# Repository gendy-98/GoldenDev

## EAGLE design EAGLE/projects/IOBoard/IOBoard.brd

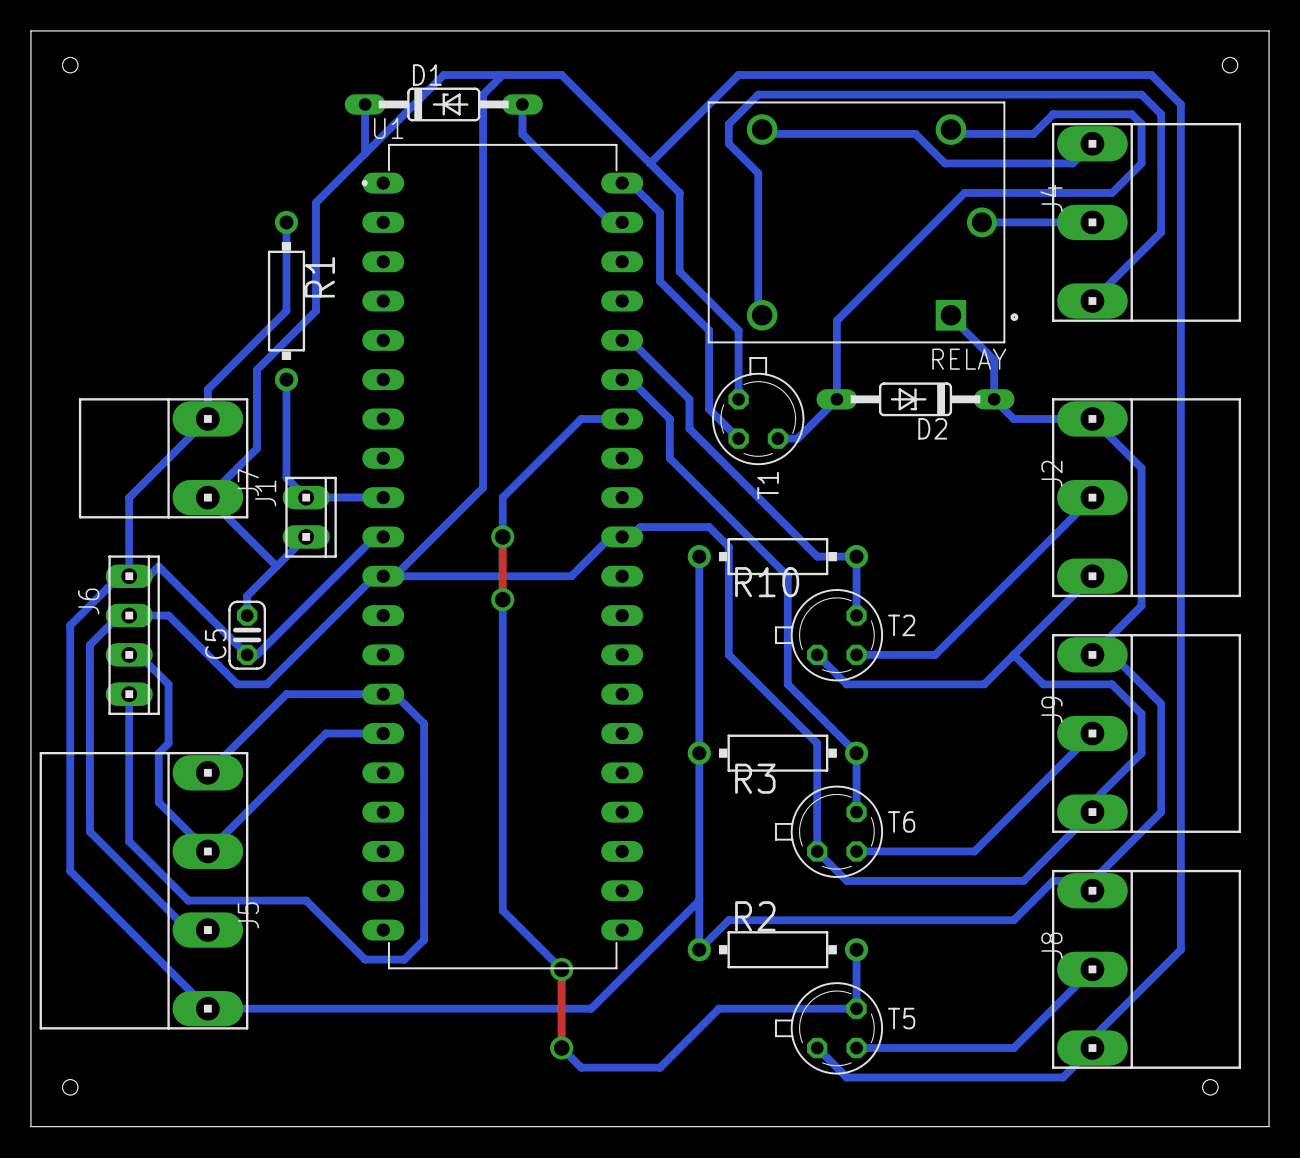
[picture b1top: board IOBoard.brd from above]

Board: 2 copper layers, 80.0 x 70.8 mm, 21 parts (0 on the bottom side), 17 nets.

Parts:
C5: C025-024X044
D1, D2: 1N821; DO35Z10
J1: 10X02MTA
J2, J4, J8, J9: 10X05MTA_MYV
J5: 10X07MTA_MYV
J6: 10X04MTA
J7: 10X03MTA_MYV
R1, R2, R3, R10: HPS58
RELAY: SRD-05VDC-SL-C; RELAY_SRD-05VDC-SL-C
T1, T2, T5, T6: 2N2222; TO18
U1: ATMEGA32A-PU; DIP1540W47P254L5320H635Q40B

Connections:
GND: C5.2, D1.C, J1.1, J2.1, J5.5, J6.3, J7.3, J8.1, J9.1, T1.1, T2.1, T5.1, T6.1, U1.11, U1.31
unnamed: J4.5, RELAY.NO
unnamed: J4.3, RELAY.COM
unnamed: J4.1, RELAY.NC
unnamed: D2.A, RELAY.A2, T1.3
unnamed: J8.3, T5.2
unnamed: J2.3, T2.2
unnamed: J9.3, T6.2
PA0: T1.2, U1.40
PA1: D1.A, U1.39
PA4: R10.2, T2.3, U1.36
PA5: R3.2, T6.3, U1.35
PA6: R2.2, T5.3, U1.34
RST: J1.2, R1.2, U1.9
RX: J5.3, J6.2, U1.15
TX: J5.1, J6.1, U1.14
VCC: C5.1, D2.C, J2.5, J5.7, J6.4, J7.1, J8.5, J9.5, R1.1, R2.1, R3.1, R10.1, RELAY.A1, U1.10

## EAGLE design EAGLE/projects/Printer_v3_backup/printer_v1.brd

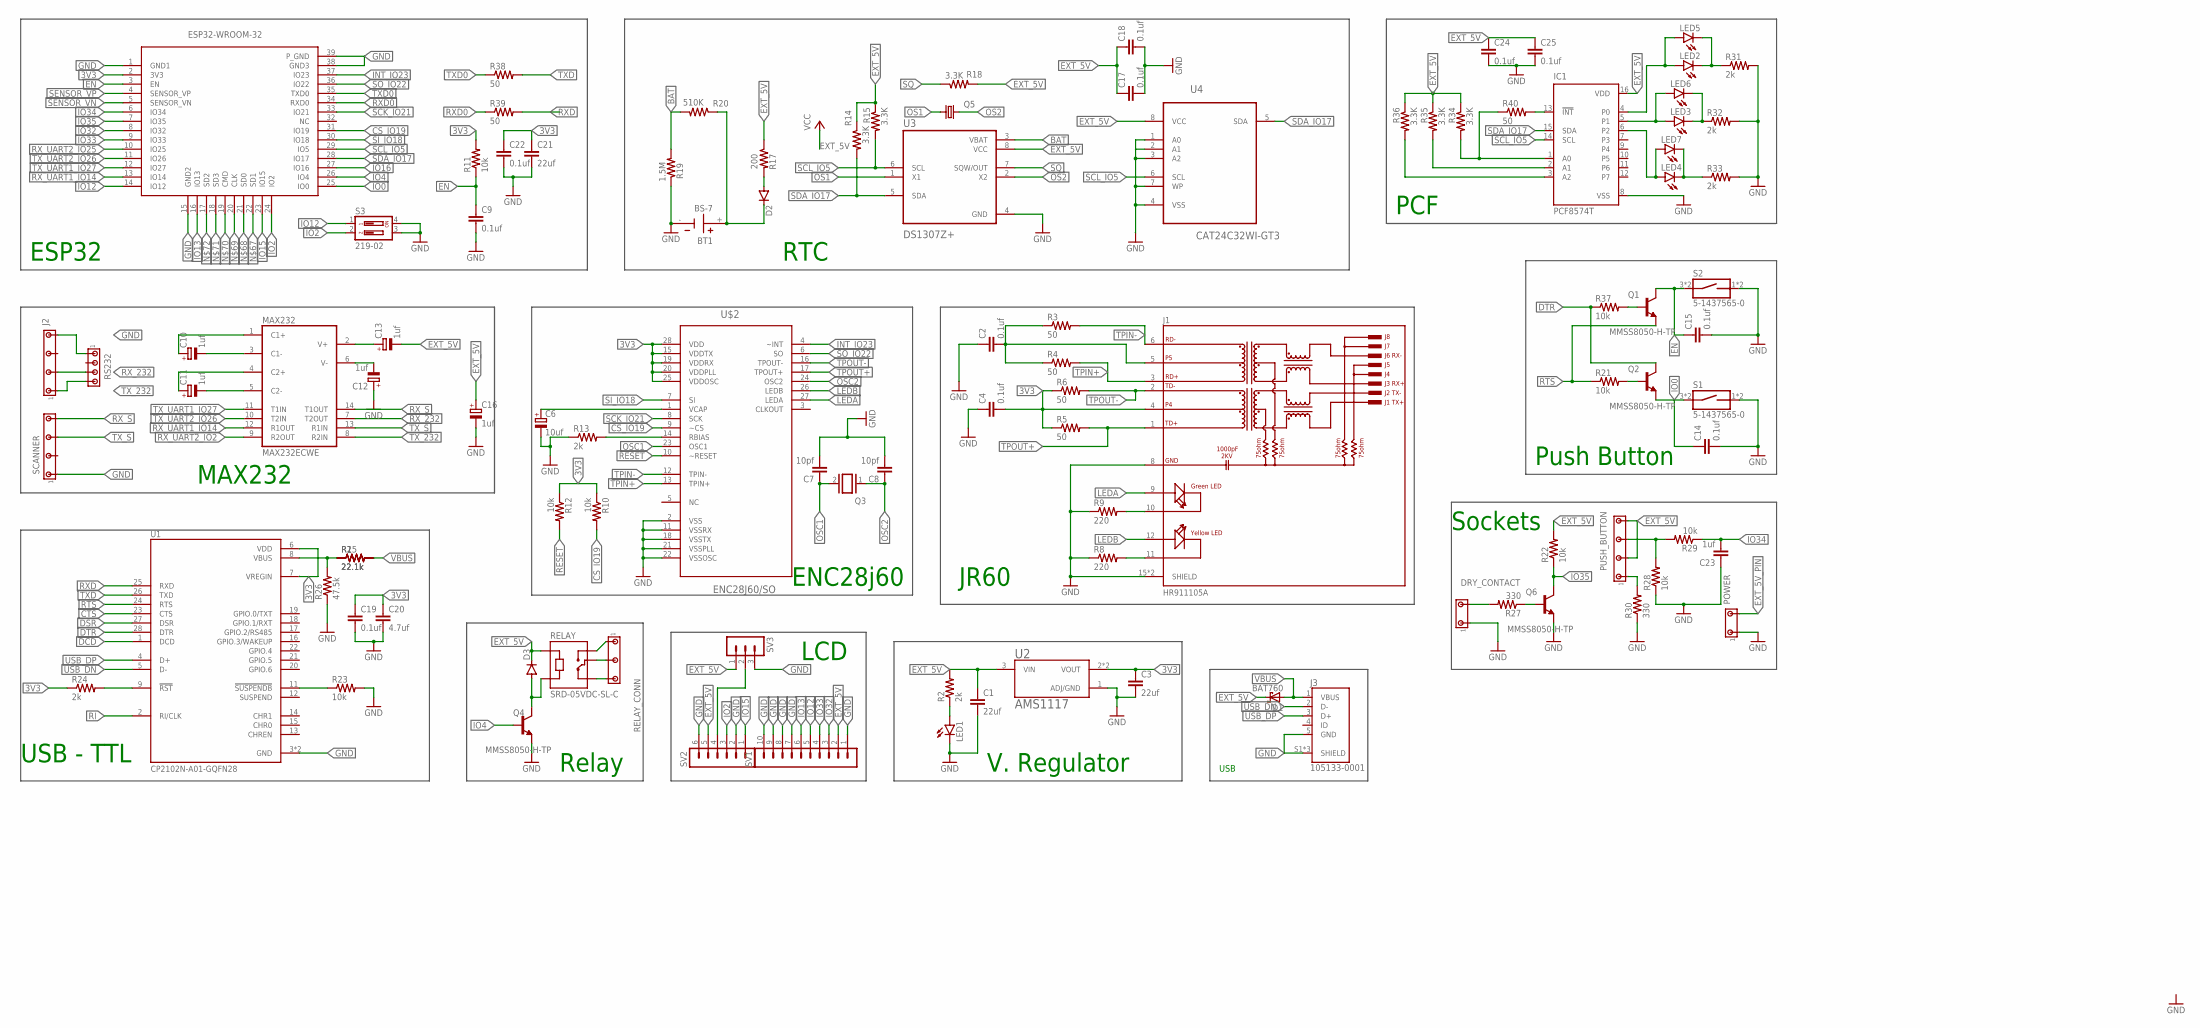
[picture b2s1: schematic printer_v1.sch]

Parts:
BT1: BS-7; BAT_BS-7
C1, C3, C21: 22uf; C0603
C2, C4, C9, C14, C15, C17, C18, C19, C22, C24, C25: 0.1uf; C0402
C6: 10uf; 153CLV-0405
C7, C8: 10pf; C0402
C10, C11, C12, C13, C16: 1uf; A/3216-18R
C20: 4.7uf; C0402
C23: 1uf; C0603
D1: BAT760; SOD323(F)
D2, D3: DIODE-DO-214AC; DO-214AC
DRY_CONTACT: MTA03-100_MYV; 10X03MTA_MYV
IC1: PCF8574T; SO16W
J1: HR911105A; HANRUN_HR911105A
J2: MTA07-100_MYV; 10X07MTA_MYV
J3: 105133-0001; MOLEX_105133-0001
LED1, LED2, LED3, LED4: LEDSML0603; SML0603
LED5, LED6, LED7: LED5MM
MAX232: MAX232ECWE; SO16L
POWER: MTA03-100_MYV; 10X03MTA_MYV
PUSH_BUTTON: MTA07-100_MYV; 10X07MTA_MYV
Q1, Q2, Q4, Q6: MMSS8050-H-TP; TRANS_MMSS8050-H-TP
Q3: XTAL/S; QS
Q5: KX-327-NHF; 3.2X1.5
R1, R25: 22.1k; R0402
R2, R13, R24, R31, R32, R33: 2k; R0402
R3, R4, R5, R6, R38, R39, R40: 50; R0402
R8, R9: 220; R0402
R10, R11, R12, R21, R22, R23, R28, R29, R37: 10k; R0402
R14, R15, R18, R34, R35, R36: 3.3K; R0603
R17: 200; R0603
R19: 1.5M; R0603
R20: 510K; R0603
R26: 47.5k; R0402
R27, R30: 330; R0402
RELAY: SRD-05VDC-SL-C; RELAY_SRD-05VDC-SL-C
RELAY_CONN: MTA05-156_MYVSPACE1; 10X05MTA_MYV
RS232: MTA04-100; 10X04MTA
S1, S2: 5-1437565-0; SW_5-1437565-0
S3: 219-02; CTS-219-02
SCANNER: MTA07-100_MYV; 10X07MTA_MYV
SV1: MA10-1
SV2: MA06-1
SV3: MA03-1
U1: CP2102N-A01-GQFN28; QFN50P500X500X80-29N
U2: AMS1117; SOT229P700X180-4N
U3: DS1307Z+; SOIC127P600X175-8N
U4: CAT24C32WI-GT3; SOIC127P600X175-8N
U$2: ENC28J60/SO; SOIC127P1034X264-28N
U$3: ESP32-WROOM-32

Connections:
3V3: C3.1, C4.2, C19.1, C20.1, C21.1, C22.1, J1.4, R5.1, R6.1, R10.1, R11.2, R12.1, R24.1, U1.6 (VDD), U1.7 (VREGIN), U2.2 (VOUT), U2.4 (VOUT), U$2.15 (VDDTX), U$2.19 (VDDRX), U$2.20 (VDDPLL), U$2.25 (VDDOSC), U$2.28 (VDD), U$3.2 (3V3)
BAT: R19.2, R20.2, U3.3 (VBAT)
CS_IO19: R10.2, U$2.9 (~CS), U$3.31 (IO19)
CTS: U1.23 (CTS)
DCD: U1.1 (DCD)
DSR: U1.27 (DSR)
DTR: Q2.3 (C), R37.1, U1.28 (DTR)
EN: C9.1, C15.1, Q1.3 (C), R11.1, S2.3 (1), S2.4 (1), U$3.3 (EN)
EXT_5V: C1.1, C13.-, C16.+, C17.1, C18.1, C24.1, C25.1, D1.1 (K), D3.C, IC1.16 (VDD), MAX232.16 (VCC), PUSH_BUTTON.3, PUSH_BUTTON.7, R2.2, R14.1, R15.1, R17.1, R18.2, R22.2, R34.1, R35.1, R36.1, RELAY.A1, SV1.2, SV2.5, SV3.1, U2.3 (VIN), U3.8 (VCC), U4.8 (VCC)
EXT_5V_PIN: POWER.3
GND: BT1.-, C1.2, C2.1, C3.2, C4.1, C6.-, C7.2, C8.2, C9.2, C12.+, C14.2, C15.2, C16.-, C17.2, C18.2, C19.2, C20.2, C21.2, C22.2, C23.1, C24.2, C25.2, DRY_CONTACT.1, IC1.8 (VSS), J1.8 (GND), J1.15 (SHIELD), J1.16 (SHIELD), J2.7, J3.5 (GND), J3.S1 (SHIELD), J3.S2 (SHIELD), J3.S3 (SHIELD), LED1.C, MAX232.15 (GND), POWER.1, Q4.2 (E), Q6.2 (E), R8.1, R9.1, R13.1, R19.1, R23.2, R26.1, R28.1, R30.1, R31.2, R32.2, R33.2, RS232.1, S1.1 (2), S1.2, S2.1 (2), S2.2, S3.3, S3.4, SCANNER.1, SV1.1, SV1.7, SV1.8, SV1.9, SV1.10, SV2.2, SV2.6, SV3.3, U1.3 (GND), U1.29 (GND), U2.1 (ADJ/GND), U3.4 (GND), U4.1 (A0), U4.2 (A1), U4.3 (A2), U4.4 (VSS), U4.7 (WP), U$2.2 (VSS), U$2.11 (VSSRX), U$2.18 (VSSTX), U$2.21 (VSSPLL), U$2.22 (VSSOSC), U$3.1 (GND1), U$3.15 (GND2), U$3.38 (GND3), U$3.39 (P_GND)
INT_IO23: U$2.4 (~INT), U$3.37 (IO23)
IO0: C14.1, Q2.2 (E), S1.3 (1), S1.4 (1), U$3.25 (IO0)
IO2: S3.2, SV2.3, U$3.24 (IO2)
IO4: Q4.1 (B), U$3.26 (IO4)
IO12: S3.1, SV1.5, U$3.14 (IO12)
IO13: SV1.6, U$3.16 (IO13)
IO15: SV2.1, U$3.23 (IO15)
IO16: U$3.27 (IO16)
IO32: SV1.3, U$3.8 (IO32)
IO33: SV1.4, U$3.9 (IO33)
IO34: C23.2, R29.1, U$3.6 (IO34)
IO35: Q6.3 (C), R22.1, U$3.7 (IO35)
LEDA: J1.9 (GA), U$2.27 (LEDA)
LEDB: J1.12 (YA), U$2.26 (LEDB)
unnamed: LED1.A, R2.1
unnamed: Q1.1 (B), R37.2
unnamed: Q2.1 (B), R21.2
unnamed: R1.1, R25.1, R26.2, U1.8 (VBUS)
unnamed: SV2.4, SV3.2
unnamed: R23.1, U1.11 (!SUSPENDB)
unnamed: J1.11 (YC), R8.2
unnamed: C2.2, J1.5, R3.1, R4.1
unnamed: J1.10 (GC), R9.2
unnamed: R13.2, U$2.14 (RBIAS)
unnamed: C6.+, U$2.1 (VCAP)
unnamed: C10.+, MAX232.1 (C1+)
unnamed: C10.-, MAX232.3 (C1-)
unnamed: C11.-, MAX232.5 (C2-)
unnamed: R24.2, U1.9 (!RST)
unnamed: C11.+, MAX232.4 (C2+)
unnamed: C12.-, MAX232.6 (V-)
unnamed: C13.+, MAX232.2 (V+)
unnamed: RELAY.NC, RELAY_CONN.5
unnamed: RELAY.COM, RELAY_CONN.3
unnamed: LED2.C, LED5.K (C), R31.1
unnamed: IC1.13 (!INT), R40.2
unnamed: RELAY.NO, RELAY_CONN.1
unnamed: D3.A, Q4.3 (C), RELAY.A2
unnamed: D2.A, R17.2
unnamed: BT1.+, D2.C, R20.1
unnamed: Q6.1 (B), R27.1
unnamed: PUSH_BUTTON.5, R28.2, R29.2
unnamed: DRY_CONTACT.3, R27.2
unnamed: IC1.4 (P0), LED2.A, LED5.A
unnamed: IC1.5 (P1), LED3.A, LED6.A
unnamed: IC1.6 (P2), LED4.A, LED7.A
unnamed: PUSH_BUTTON.1, R30.2
unnamed: IC1.1 (A0), R34.2, R40.1
unnamed: IC1.2 (A1), R35.2
unnamed: IC1.3 (A2), R36.2
unnamed: LED3.C, LED6.K (C), R32.1
unnamed: LED4.C, LED7.K (C), R33.1
OS1: Q5.1, U3.1 (X1)
OS2: Q5.2, U3.2 (X2)
OSC1: C7.1, Q3.2, U$2.23 (OSC1)
OSC2: C8.1, Q3.1, U$2.24 (OSC2)
RESET: R12.2, U$2.10 (~RESET)
RI: U1.2 (RI/CLK)
RTS: Q1.2 (E), R21.1, U1.24 (RTS)
RXD: R39.2, U1.25 (RXD)
RXD0: R39.1, U$3.34 (RXD0)
RX_232: J2.3, MAX232.7 (T2OUT), RS232.3
RX_S: MAX232.14 (T1OUT), SCANNER.7
RX_UART1_IO14: MAX232.12 (R1OUT), U$3.13 (IO14)
RX_UART2_IO2: MAX232.9 (R2OUT)
RX_UART2_IO25: U$3.10 (IO25)
SCK_IO21: U$2.8 (SCK), U$3.33 (IO21)
SCL_IO5: IC1.14 (SCL), R15.2, U3.6 (SCL), U4.6 (SCL), U$3.29 (IO5)
SDA_IO17: IC1.15 (SDA), R14.2, U3.5 (SDA), U4.5 (SDA), U$3.28 (IO17)
SENSOR_VN: U$3.5 (SENSOR_VN)
SENSOR_VP: U$3.4 (SENSOR_VP)
SI_IO18: U$2.7 (SI), U$3.30 (IO18)
SO_IO22: U$2.6 (SO), U$3.36 (IO22)
SQ: R18.1, U3.7 (SQW/OUT)
TPIN+: J1.3 (RD+), R4.2, U$2.13 (TPIN+)
TPIN-: J1.6 (RD-), R3.2, U$2.12 (TPIN-)
TPOUT+: J1.1 (TD+), R5.2, U$2.17 (TPOUT+)
TPOUT-: J1.2 (TD-), R6.2, U$2.16 (TPOUT-)
TXD: R38.2, U1.26 (TXD)
TXD0: R38.1, U$3.35 (TXD0)
TX_232: J2.1, MAX232.8 (R2IN), RS232.4
TX_S: MAX232.13 (R1IN), SCANNER.5
TX_UART1_IO27: MAX232.11 (T1IN), U$3.12 (IO27)
TX_UART2_IO26: MAX232.10 (T2IN), U$3.11 (IO26)
USB_DN: J3.2 (D-), U1.5 (D-)
USB_DP: J3.3 (D+), U1.4 (D+)
VBUS: D1.2 (A), J3.1 (VBUS), R1.2, R25.2

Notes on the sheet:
PCF
ESP32
RTC
Push Button
JR60
ENC28j60
MAX232
USB - TTL
Relay
LCD
V. Regulator
USB
Sockets

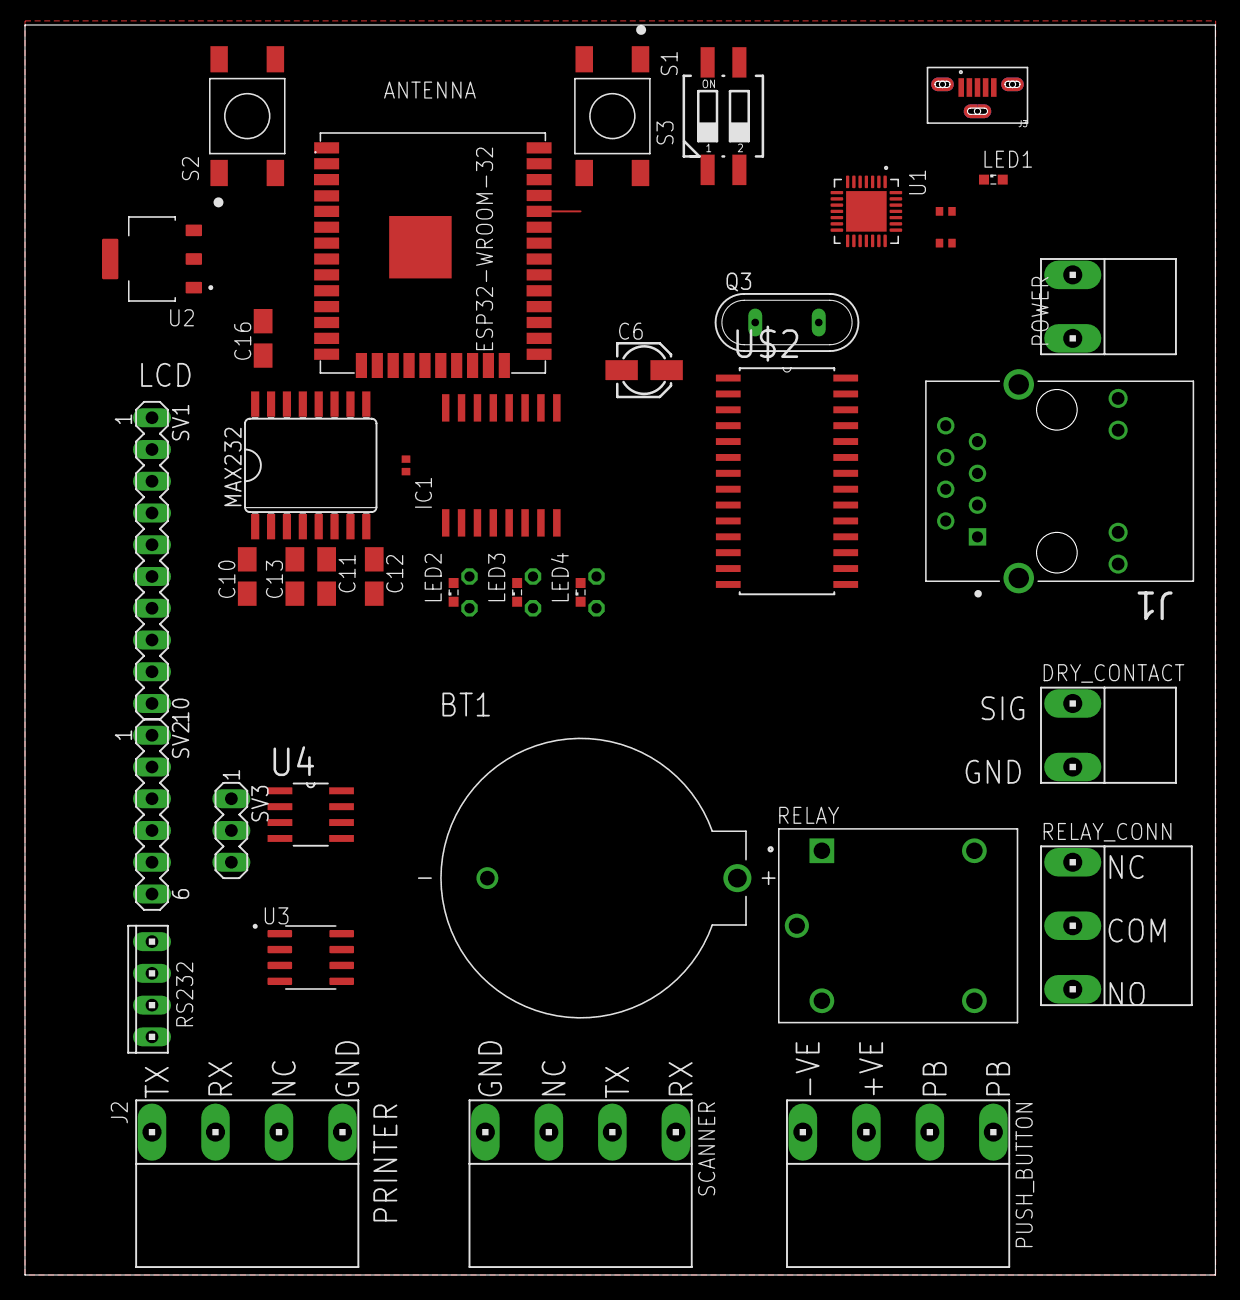
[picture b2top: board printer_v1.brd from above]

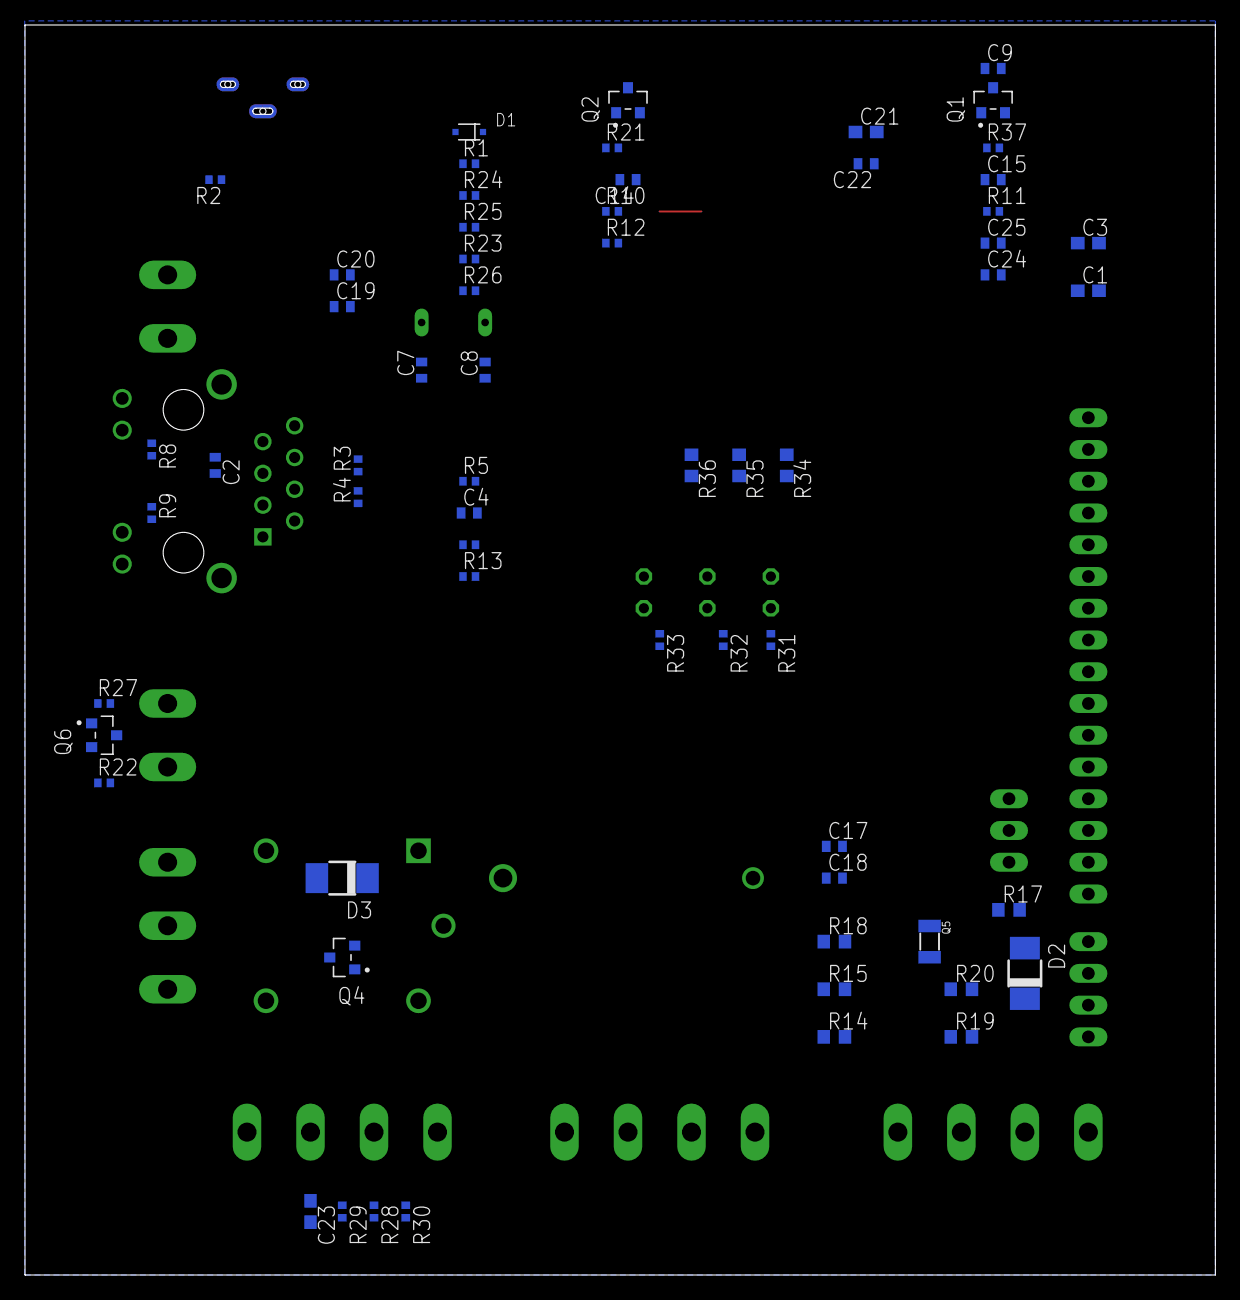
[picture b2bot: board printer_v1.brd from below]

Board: 2 copper layers, 95.2 x 100.0 mm, 103 parts (62 on the bottom side), 88 nets.

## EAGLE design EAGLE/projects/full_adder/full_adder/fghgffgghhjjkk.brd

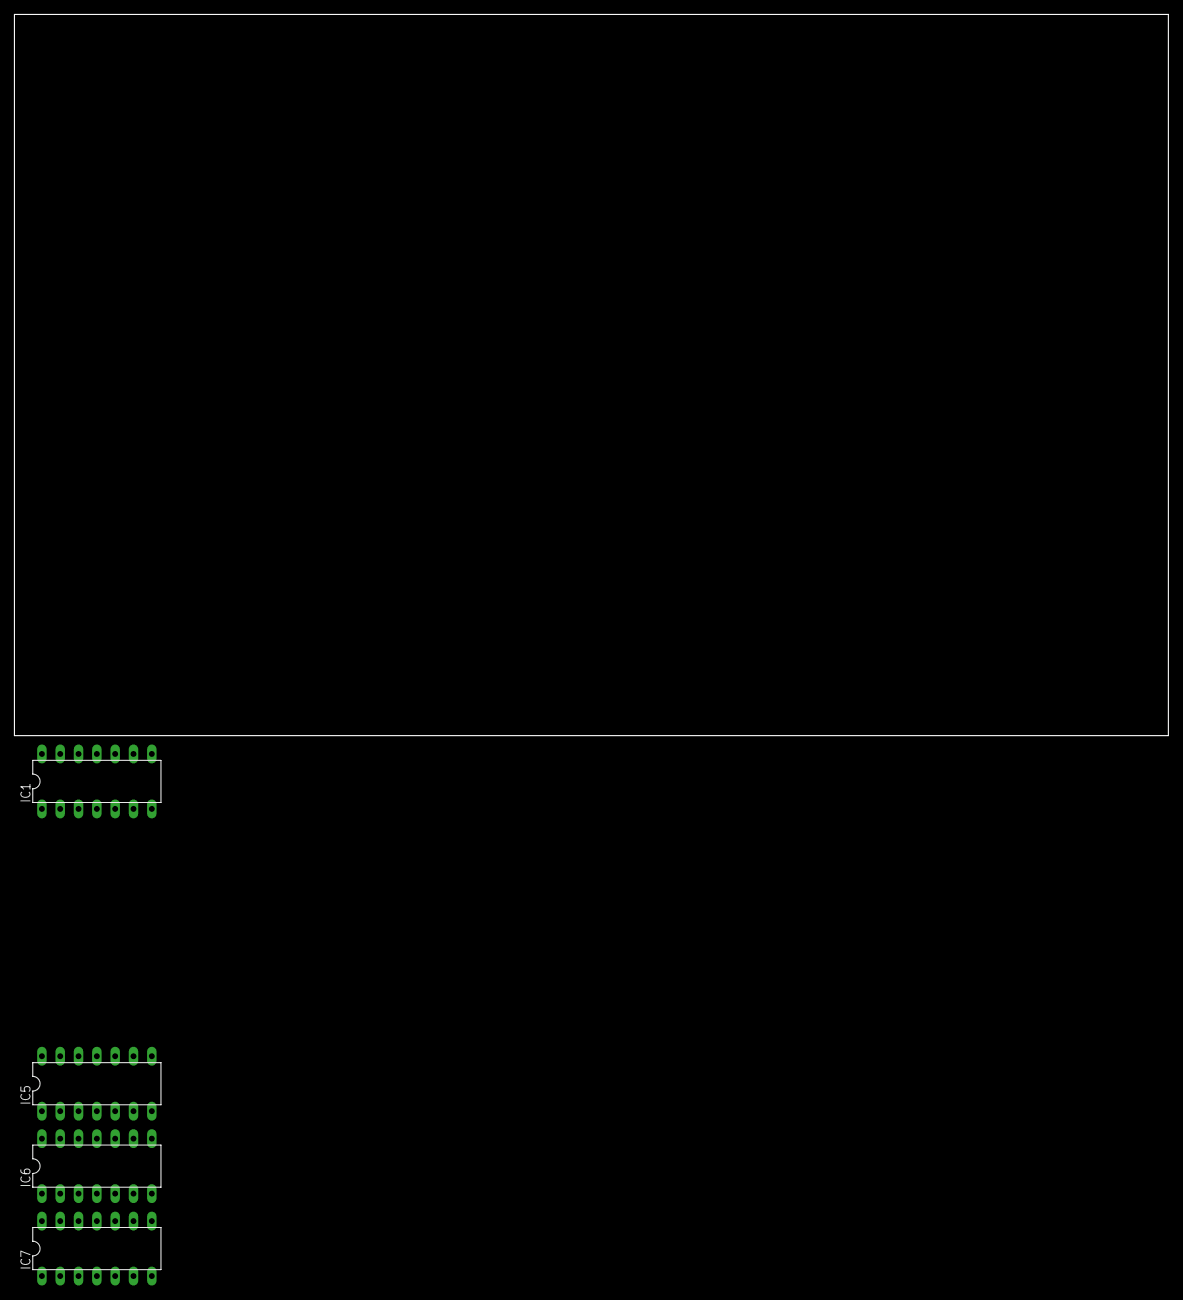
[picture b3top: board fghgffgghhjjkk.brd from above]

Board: 2 copper layers, 160.0 x 100.0 mm, 4 parts (0 on the bottom side), 2 nets, no tracks yet.

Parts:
IC1: 74ALS04N; DIL14
IC5, IC6, IC7: 74LS32N; DIL14

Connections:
GND: IC1.7, IC5.7, IC6.7, IC7.7
VCC: IC1.14, IC5.14, IC6.14, IC7.14

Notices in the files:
parts and their libraries:
crystal-geyer_V1_0: Copyright: Geyer-Electronic
